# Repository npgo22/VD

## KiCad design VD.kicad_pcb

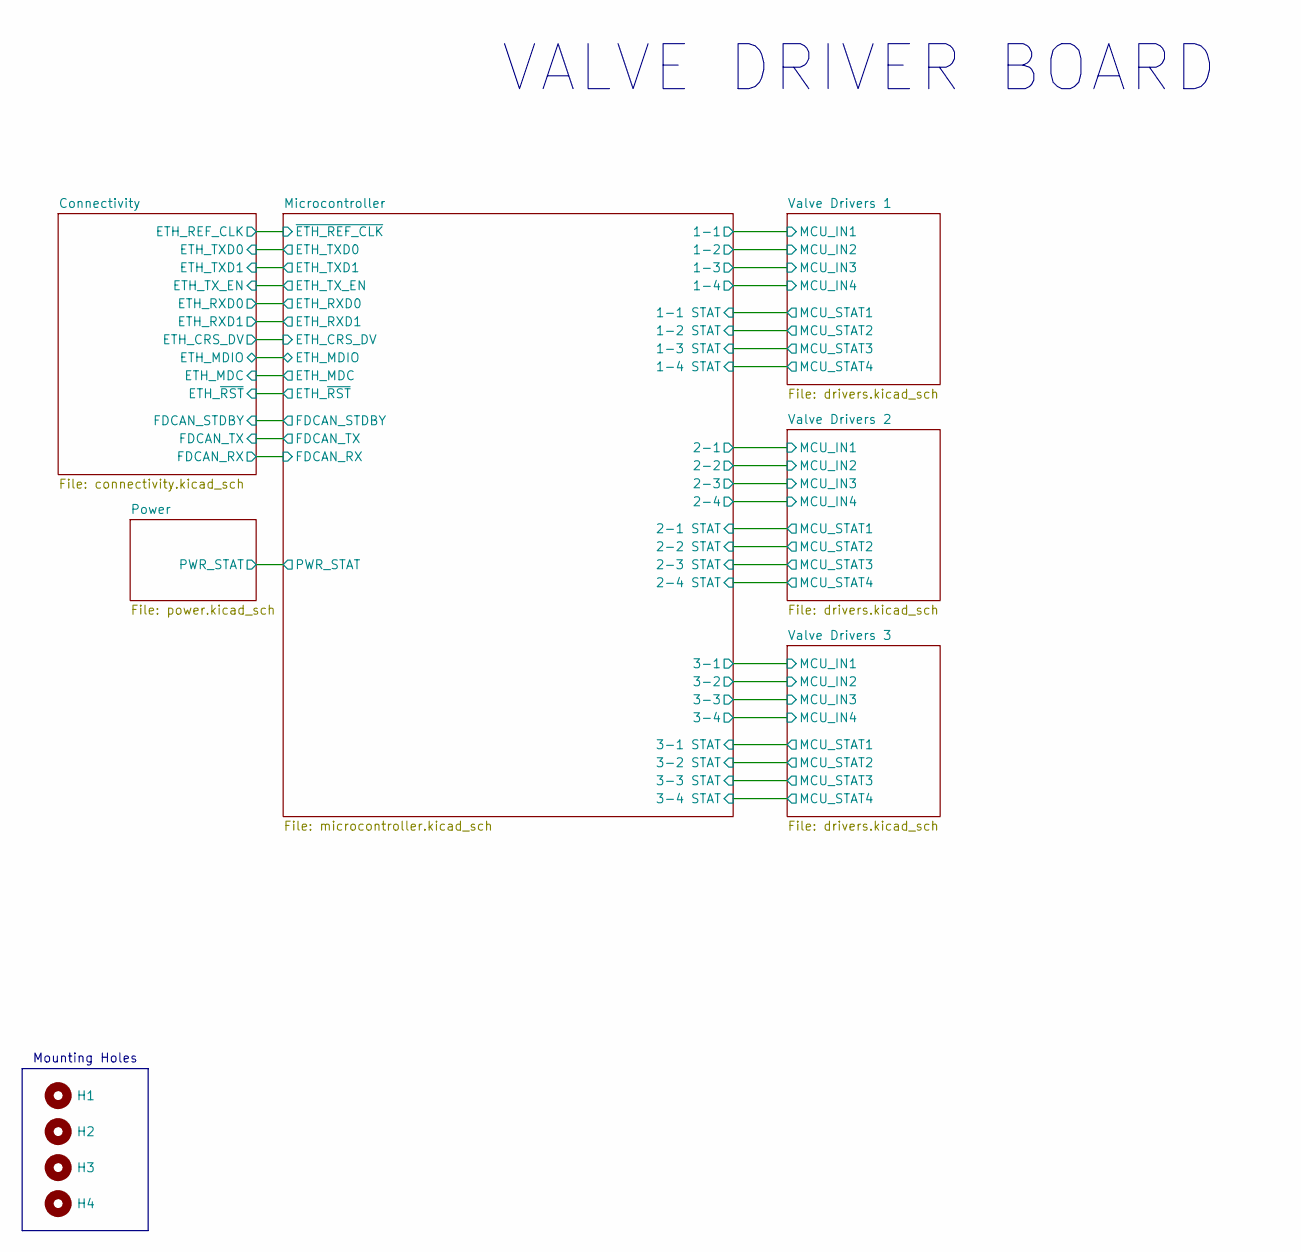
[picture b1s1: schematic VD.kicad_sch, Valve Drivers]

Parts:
H1, H2, H3, H4: MountingHole; MountingHole_3.2mm_M3

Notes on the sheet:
VALVE DRIVER BOARD
Mounting Holes

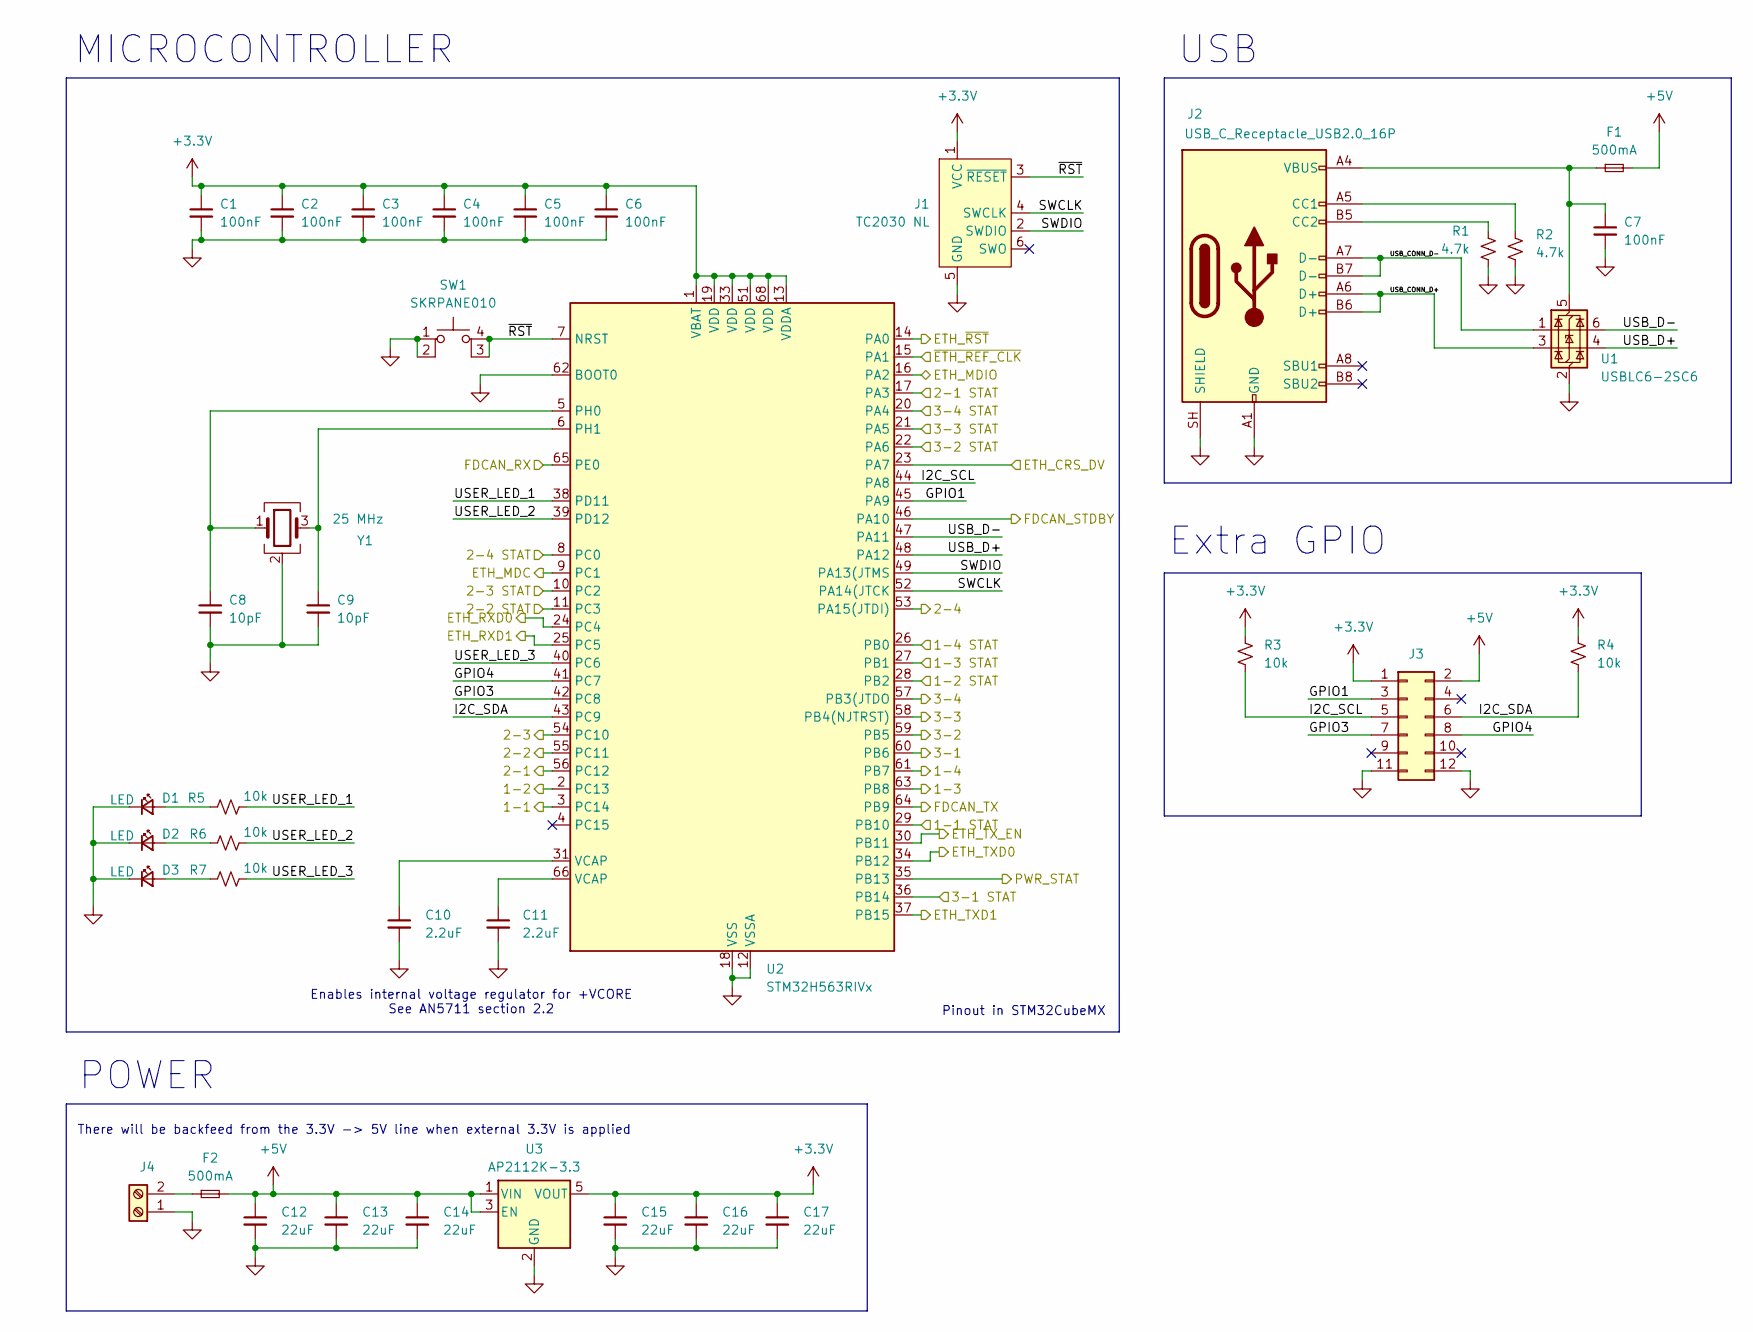
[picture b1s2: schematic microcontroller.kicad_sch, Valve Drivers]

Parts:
C1, C2, C3, C4, C5, C6, C7: 100nF; C_0603
C8, C9: 10pF; C_0603
C10, C11: 2.2uF; C_0603
C12, C13, C14, C15, C16, C17: 22uF; C_0805
D1, D2, D3: LED; LED_0603
F1, F2: 500mA; Fuse_0805_2012Metric
J1: TC2030 NL; Tag-Connect_TC2030-IDC-NL_2x03_P1.27mm_Vertical
J2: USB_C_Receptacle_USB2.0_16P; USB_C_Receptacle_HRO_TYPE-C-31-M-12
J3: Conn_02x06_Top_Bottom; IDC-Header_2x06_P2.54mm_Vertical
J4: Screw_Terminal_01x02; TerminalBlock_Phoenix_MPT-0,5-2-2.54_1x02_P2.54mm_Horizontal
R1, R2: 4.7k; R_0603
R3, R4, R5, R6, R7: 10k; R_0603
SW1: SKRPANE010
U1: USBLC6-2SC6; SOT-23-6
U2: STM32H563RIVx; QFN-68-1EP_8x8mm_P0.4mm_EP6.4x6.4mm
U3: AP2112K-3.3; SOT-23-5
Y1: 25 MHz; 3225-4P-L

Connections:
+3.3V: C1.1, C2.1, C3.1, C4.1, C5.1, C6.1, C15.1, C16.1, C17.1, J1.1 (VCC), J3.1, R3.1, R4.1, U2.1 (VBAT), U2.13 (VDDA), U2.19 (VDD), U2.33 (VDD), U2.51 (VDD), U2.68 (VDD), U3.5 (VOUT); also elsewhere on the board
+5V: C12.1, C13.1, C14.1, F1.2, F2.2, J3.2, U3.1 (VIN), U3.3 (EN); also elsewhere on the board
/Connectivity/ETH_CRS_DV: U2.23 (PA7); also elsewhere on the board
/Connectivity/ETH_MDC: U2.9 (PC1); also elsewhere on the board
/Connectivity/ETH_MDIO: U2.16 (PA2); also elsewhere on the board
/Connectivity/ETH_REF_CLK: U2.15 (PA1); also elsewhere on the board
/Connectivity/ETH_RXD0: U2.24 (PC4); also elsewhere on the board
/Connectivity/ETH_RXD1: U2.25 (PC5); also elsewhere on the board
/Connectivity/ETH_TXD0: U2.34 (PB12); also elsewhere on the board
/Connectivity/ETH_TXD1: U2.37 (PB15); also elsewhere on the board
/Connectivity/ETH_TX_EN: U2.30 (PB11); also elsewhere on the board
/Connectivity/ETH_~RST: U2.14 (PA0); also elsewhere on the board
/Connectivity/FDCAN_RX: U2.65 (PE0); also elsewhere on the board
/Connectivity/FDCAN_STDBY: U2.46 (PA10); also elsewhere on the board
/Connectivity/FDCAN_TX: U2.64 (PB9); also elsewhere on the board
/Microcontroller/1-1: U2.3 (PC14); also elsewhere on the board
/Microcontroller/1-1 STAT: U2.29 (PB10); also elsewhere on the board
/Microcontroller/1-2: U2.2 (PC13); also elsewhere on the board
/Microcontroller/1-2 STAT: U2.28 (PB2); also elsewhere on the board
/Microcontroller/1-3: U2.63 (PB8); also elsewhere on the board
/Microcontroller/1-3 STAT: U2.27 (PB1); also elsewhere on the board
/Microcontroller/1-4: U2.61 (PB7); also elsewhere on the board
/Microcontroller/1-4 STAT: U2.26 (PB0); also elsewhere on the board
/Microcontroller/2-1: U2.56 (PC12); also elsewhere on the board
/Microcontroller/2-1 STAT: U2.17 (PA3); also elsewhere on the board
/Microcontroller/2-2: U2.55 (PC11); also elsewhere on the board
/Microcontroller/2-2 STAT: U2.11 (PC3); also elsewhere on the board
/Microcontroller/2-3: U2.54 (PC10); also elsewhere on the board
/Microcontroller/2-3 STAT: U2.10 (PC2); also elsewhere on the board
/Microcontroller/2-4: U2.53 (PA15(JTDI)); also elsewhere on the board
/Microcontroller/2-4 STAT: U2.8 (PC0); also elsewhere on the board
/Microcontroller/3-1: U2.60 (PB6); also elsewhere on the board
/Microcontroller/3-1 STAT: U2.36 (PB14); also elsewhere on the board
/Microcontroller/3-2: U2.59 (PB5); also elsewhere on the board
/Microcontroller/3-2 STAT: U2.22 (PA6); also elsewhere on the board
/Microcontroller/3-3: U2.58 (PB4(NJTRST)); also elsewhere on the board
/Microcontroller/3-3 STAT: U2.21 (PA5); also elsewhere on the board
/Microcontroller/3-4: U2.57 (PB3(JTDO); also elsewhere on the board
/Microcontroller/3-4 STAT: U2.20 (PA4); also elsewhere on the board
/Microcontroller/GPIO1: J3.3, U2.45 (PA9)
/Microcontroller/GPIO3: J3.7, U2.42 (PC8)
/Microcontroller/GPIO4: J3.8, U2.41 (PC7)
/Microcontroller/I2C_SCL: J3.5, R3.2, U2.44 (PA8)
/Microcontroller/I2C_SDA: J3.6, R4.2, U2.43 (PC9)
/Microcontroller/PWR_STAT: U2.35 (PB13); also elsewhere on the board
/Microcontroller/SWCLK: J1.4 (SWCLK), U2.52 (PA14(JTCK)
/Microcontroller/SWDIO: J1.2 (SWDIO), U2.49 (PA13(JTMS)
/Microcontroller/USB_CONN_D+: J2.A6 (D+), J2.B6 (D+), U1.3 (I/O2)
/Microcontroller/USB_CONN_D-: J2.A7 (D-), J2.B7 (D-), U1.1 (I/O1)
/Microcontroller/USB_D+: U1.4 (I/O2), U2.48 (PA12)
/Microcontroller/USB_D-: U1.6 (I/O1), U2.47 (PA11)
/Microcontroller/USER_LED_1: R5.2, U2.38 (PD11)
/Microcontroller/USER_LED_2: R6.2, U2.39 (PD12)
/Microcontroller/USER_LED_3: R7.2, U2.40 (PC6)
/Microcontroller/~RST: J1.3 (~RESET), SW1.3 (K), SW1.4 (A), U2.7 (NRST)
GND: C1.2, C2.2, C3.2, C4.2, C5.2, C6.2, C7.2, C8.2, C9.2, C10.2, C11.2, C12.2, C13.2, C14.2, C15.2, C16.2, C17.2, D1.1 (K), D2.1 (K), D3.1 (K), J1.5 (GND), J2.A1 (GND), J2.A12 (GND), J2.B1 (GND), J2.B12 (GND), J2.SH (SHIELD), J3.11, J3.12, J4.1, R1.1, R2.2, SW1.1, SW1.2, U1.2 (GND), U2.12 (VSSA), U2.18 (VSS), U2.32 (VSS), U2.50 (VSS), U2.62 (BOOT0), U2.67 (VSS), U2.69 (VSS), U3.2 (GND), Y1.2 (G), Y1.4 (G); also elsewhere on the board
unnamed: C10.1, U2.31 (VCAP)
unnamed: C11.1, U2.66 (VCAP)
unnamed: D1.2 (A), R5.1
unnamed: D2.2 (A), R6.1
unnamed: D3.2 (A), R7.1
unnamed: J2.A5 (CC1), R2.1
unnamed: J2.B5 (CC2), R1.2
unnamed: F2.1, J4.2
unnamed: C7.1, F1.1, J2.A4 (VBUS), J2.A9 (VBUS), J2.B4 (VBUS), J2.B9 (VBUS), U1.5 (VBUS)
unnamed: C8.1, U2.5 (PH0), Y1.1
unnamed: C9.1, U2.6 (PH1), Y1.3

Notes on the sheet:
Enables internal voltage regulator for +VCORE See AN5711 section 2.2
MICROCONTROLLER
There will be backfeed from the 3.3V -> 5V line when external 3.3V is applied
Extra GPIO
USB
POWER
Pinout in STM32CubeMX

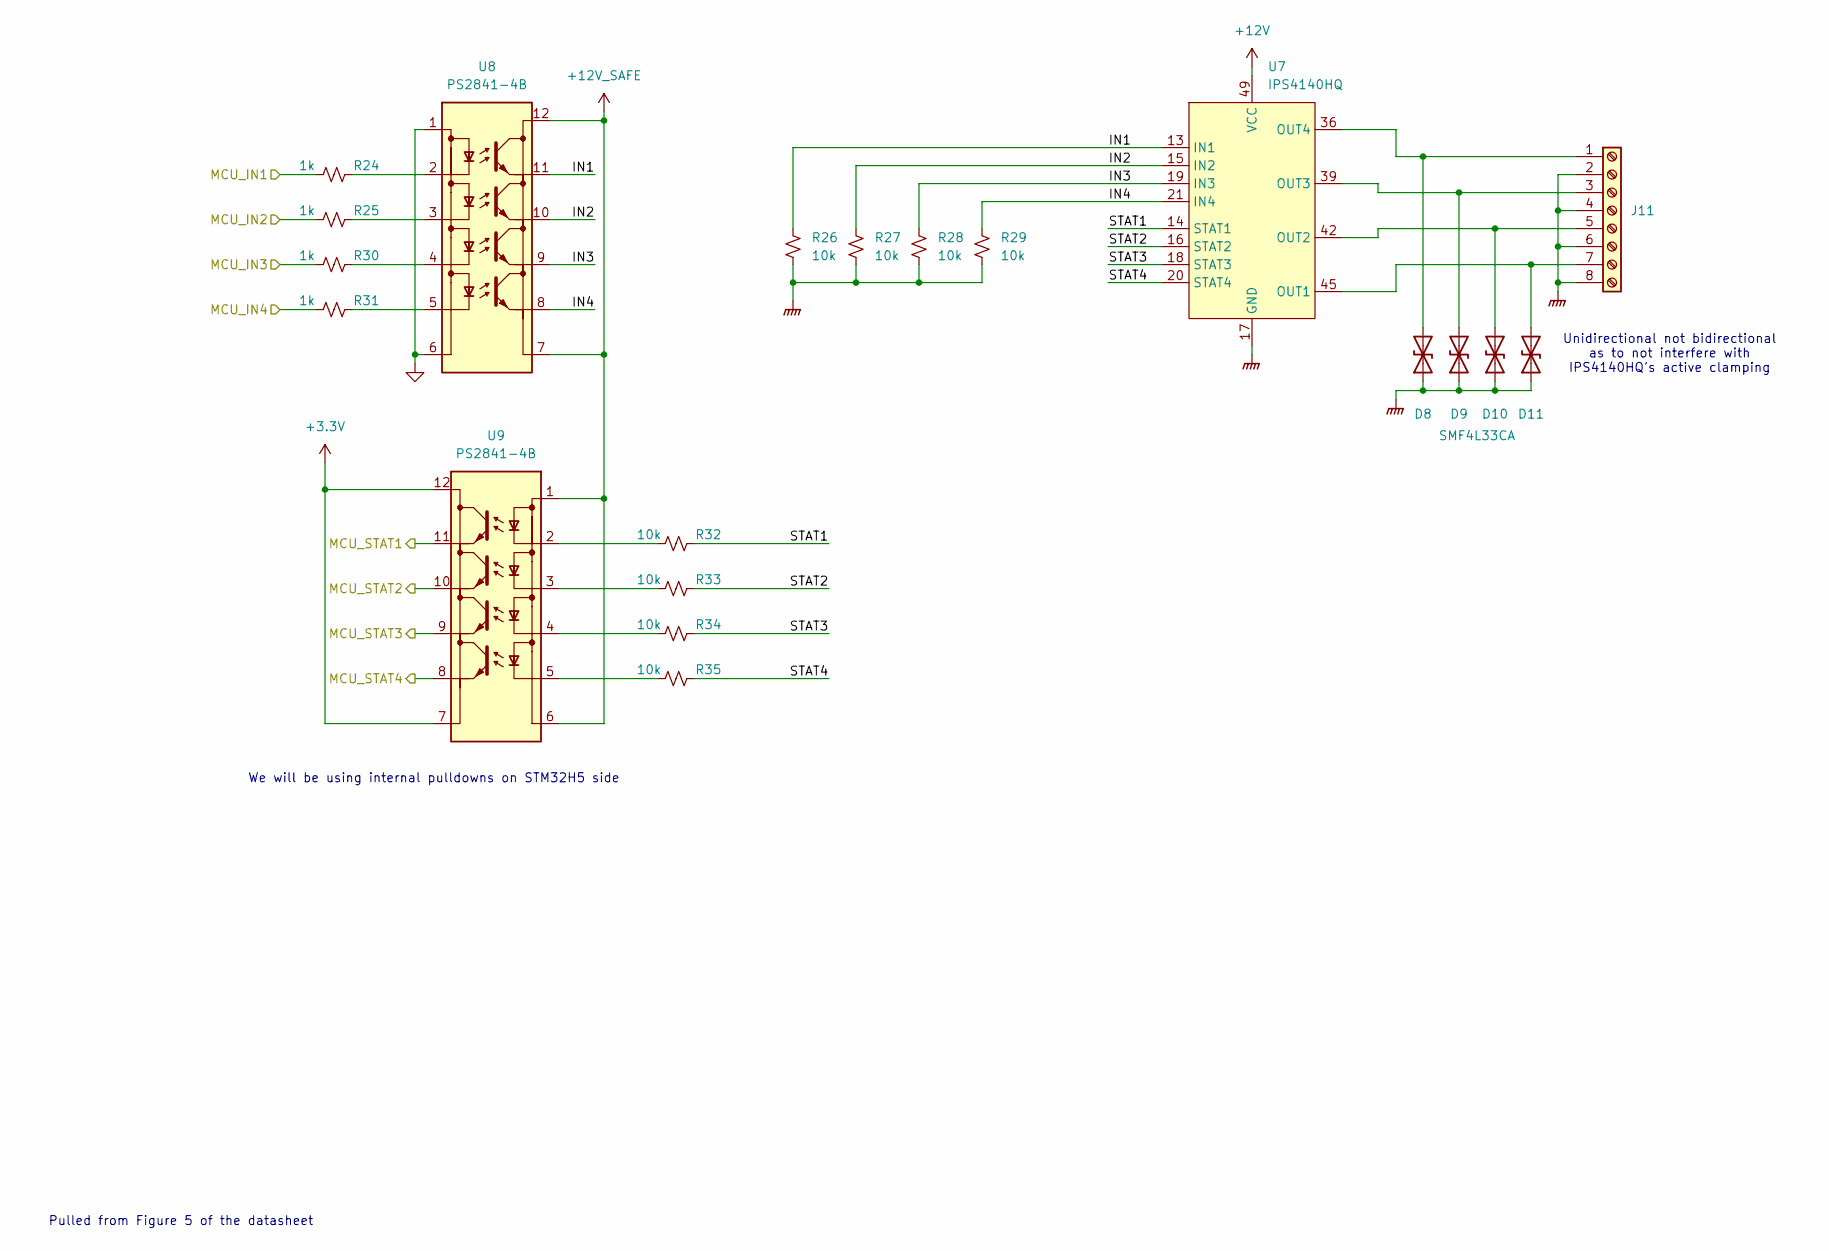
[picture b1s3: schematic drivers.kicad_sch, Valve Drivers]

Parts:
D8, D9, D10, D11: SMF4L33CA; D_SOD-123F
J11: Screw_Terminal_01x08; TerminalBlock_Phoenix_MPT-0,5-8-2.54_1x08_P2.54mm_Horizontal
R24, R25, R30, R31: 1k; R_0603
R26, R27, R28, R29, R32, R33, R34, R35: 10k; R_0603
U7: IPS4140HQ; QFN-48_EP_9.01x7.01_Pitch0.5mm
U8, U9: PS2841-4B; SOIC-12

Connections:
+3.3V: U9.7, U9.12; also elsewhere on the board
+12V: U7.49 (VCC); also elsewhere on the board
+12V_SAFE: U8.7, U8.12, U9.1, U9.6; also elsewhere on the board
/Microcontroller/1-1: R24.1; also elsewhere on the board
/Microcontroller/1-1 STAT: U9.11; also elsewhere on the board
/Microcontroller/1-2: R25.1; also elsewhere on the board
/Microcontroller/1-2 STAT: U9.10; also elsewhere on the board
/Microcontroller/1-3: R30.1; also elsewhere on the board
/Microcontroller/1-3 STAT: U9.9; also elsewhere on the board
/Microcontroller/1-4: R31.1; also elsewhere on the board
/Microcontroller/1-4 STAT: U9.8; also elsewhere on the board
/Valve Drivers 1/IN1: R26.1, U7.13 (IN1), U8.11
/Valve Drivers 1/IN2: R27.1, U7.15 (IN2), U8.10
/Valve Drivers 1/IN3: R28.1, U7.19 (IN3), U8.9
/Valve Drivers 1/IN4: R29.1, U7.21 (IN4), U8.8
/Valve Drivers 1/STAT1: R32.2, U7.14 (STAT1)
/Valve Drivers 1/STAT2: R33.2, U7.16 (STAT2)
/Valve Drivers 1/STAT3: R34.2, U7.18 (STAT3)
/Valve Drivers 1/STAT4: R35.2, U7.20 (STAT4)
GND: U8.1, U8.6; also elsewhere on the board
GNDPWR: D8.1 (A1), D9.1 (A1), D10.1 (A1), D11.1 (A1), J11.2, J11.4, J11.6, J11.8, R26.2, R27.2, R28.2, R29.2, U7.17 (GND); also elsewhere on the board
unnamed: D8.2 (A2), J11.1, U7.36 (OUT4), U7.37 (OUT4), U7.38 (OUT4)
unnamed: D9.2 (A2), J11.3, U7.39 (OUT3), U7.40 (OUT3), U7.41 (OUT3)
unnamed: D10.2 (A2), J11.5, U7.42 (OUT2), U7.43 (OUT2), U7.44 (OUT2)
unnamed: D11.2 (A2), J11.7, U7.45 (OUT1), U7.46 (OUT1), U7.47 (OUT1)
unnamed: R24.2, U8.2
unnamed: R25.2, U8.3
unnamed: R30.2, U8.4
unnamed: R31.2, U8.5
unnamed: R32.1, U9.2
unnamed: R33.1, U9.3
unnamed: R34.1, U9.4
unnamed: R35.1, U9.5

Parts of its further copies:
D12, D13, D14, D15, D16, D17, D18, D19: SMF4L33CA; D_SOD-123F
J12, J13: Screw_Terminal_01x08; TerminalBlock_Phoenix_MPT-0,5-8-2.54_1x08_P2.54mm_Horizontal
R36, R37, R42, R43, R48, R49, R54, R55: 1k; R_0603
R38, R39, R40, R41, R44, R45, R46, R47, R50, R51, R52, R53, R56, R57, R58, R59: 10k; R_0603
U10, U13: IPS4140HQ; QFN-48_EP_9.01x7.01_Pitch0.5mm
U11, U12, U14, U15: PS2841-4B; SOIC-12

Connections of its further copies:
+3.3V: U12.7, U12.12, U15.7, U15.12; also elsewhere on the board
+12V: U10.49 (VCC), U13.49 (VCC); also elsewhere on the board
+12V_SAFE: U11.7, U11.12, U12.1, U12.6, U14.7, U14.12, U15.1, U15.6; also elsewhere on the board
/Microcontroller/2-1: R36.1; also elsewhere on the board
/Microcontroller/2-1 STAT: U12.11; also elsewhere on the board
/Microcontroller/2-2: R37.1; also elsewhere on the board
/Microcontroller/2-2 STAT: U12.10; also elsewhere on the board
/Microcontroller/2-3: R42.1; also elsewhere on the board
/Microcontroller/2-3 STAT: U12.9; also elsewhere on the board
/Microcontroller/2-4: R43.1; also elsewhere on the board
/Microcontroller/2-4 STAT: U12.8; also elsewhere on the board
/Microcontroller/3-1: R48.1; also elsewhere on the board
/Microcontroller/3-1 STAT: U15.11; also elsewhere on the board
/Microcontroller/3-2: R49.1; also elsewhere on the board
/Microcontroller/3-2 STAT: U15.10; also elsewhere on the board
/Microcontroller/3-3: R54.1; also elsewhere on the board
/Microcontroller/3-3 STAT: U15.9; also elsewhere on the board
/Microcontroller/3-4: R55.1; also elsewhere on the board
/Microcontroller/3-4 STAT: U15.8; also elsewhere on the board
/Valve Drivers 2/IN1: R38.1, U10.13 (IN1), U11.11
/Valve Drivers 2/IN2: R39.1, U10.15 (IN2), U11.10
/Valve Drivers 2/IN3: R40.1, U10.19 (IN3), U11.9
/Valve Drivers 2/IN4: R41.1, U10.21 (IN4), U11.8
/Valve Drivers 2/STAT1: R44.2, U10.14 (STAT1)
/Valve Drivers 2/STAT2: R45.2, U10.16 (STAT2)
/Valve Drivers 2/STAT3: R46.2, U10.18 (STAT3)
/Valve Drivers 2/STAT4: R47.2, U10.20 (STAT4)
/Valve Drivers 3/IN1: R50.1, U13.13 (IN1), U14.11
/Valve Drivers 3/IN2: R51.1, U13.15 (IN2), U14.10
/Valve Drivers 3/IN3: R52.1, U13.19 (IN3), U14.9
/Valve Drivers 3/IN4: R53.1, U13.21 (IN4), U14.8
/Valve Drivers 3/STAT1: R56.2, U13.14 (STAT1)
/Valve Drivers 3/STAT2: R57.2, U13.16 (STAT2)
/Valve Drivers 3/STAT3: R58.2, U13.18 (STAT3)
/Valve Drivers 3/STAT4: R59.2, U13.20 (STAT4)
GND: U11.1, U11.6, U14.1, U14.6; also elsewhere on the board
GNDPWR: D12.1 (A1), D13.1 (A1), D14.1 (A1), D15.1 (A1), D16.1 (A1), D17.1 (A1), D18.1 (A1), D19.1 (A1), J12.2, J12.4, J12.6, J12.8, J13.2, J13.4, J13.6, J13.8, R38.2, R39.2, R40.2, R41.2, R50.2, R51.2, R52.2, R53.2, U10.17 (GND), U13.17 (GND); also elsewhere on the board
unnamed: D12.2 (A2), J12.1, U10.36 (OUT4), U10.37 (OUT4), U10.38 (OUT4)
unnamed: D13.2 (A2), J12.3, U10.39 (OUT3), U10.40 (OUT3), U10.41 (OUT3)
unnamed: D14.2 (A2), J12.5, U10.42 (OUT2), U10.43 (OUT2), U10.44 (OUT2)
unnamed: D15.2 (A2), J12.7, U10.45 (OUT1), U10.46 (OUT1), U10.47 (OUT1)
unnamed: D16.2 (A2), J13.1, U13.36 (OUT4), U13.37 (OUT4), U13.38 (OUT4)
unnamed: D17.2 (A2), J13.3, U13.39 (OUT3), U13.40 (OUT3), U13.41 (OUT3)
unnamed: D18.2 (A2), J13.5, U13.42 (OUT2), U13.43 (OUT2), U13.44 (OUT2)
unnamed: D19.2 (A2), J13.7, U13.45 (OUT1), U13.46 (OUT1), U13.47 (OUT1)
unnamed: R36.2, U11.2
unnamed: R37.2, U11.3
unnamed: R42.2, U11.4
unnamed: R43.2, U11.5
unnamed: R44.1, U12.2
unnamed: R45.1, U12.3
unnamed: R46.1, U12.4
unnamed: R47.1, U12.5
unnamed: R48.2, U14.2
unnamed: R49.2, U14.3
unnamed: R54.2, U14.4
unnamed: R55.2, U14.5
unnamed: R56.1, U15.2
unnamed: R57.1, U15.3
unnamed: R58.1, U15.4
unnamed: R59.1, U15.5

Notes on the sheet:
Unidirectional not bidirectional as to not interfere with IPS4140HQ's active clamping
We will be using internal pulldowns on STM32H5 side
Pulled from Figure 5 of the datasheet

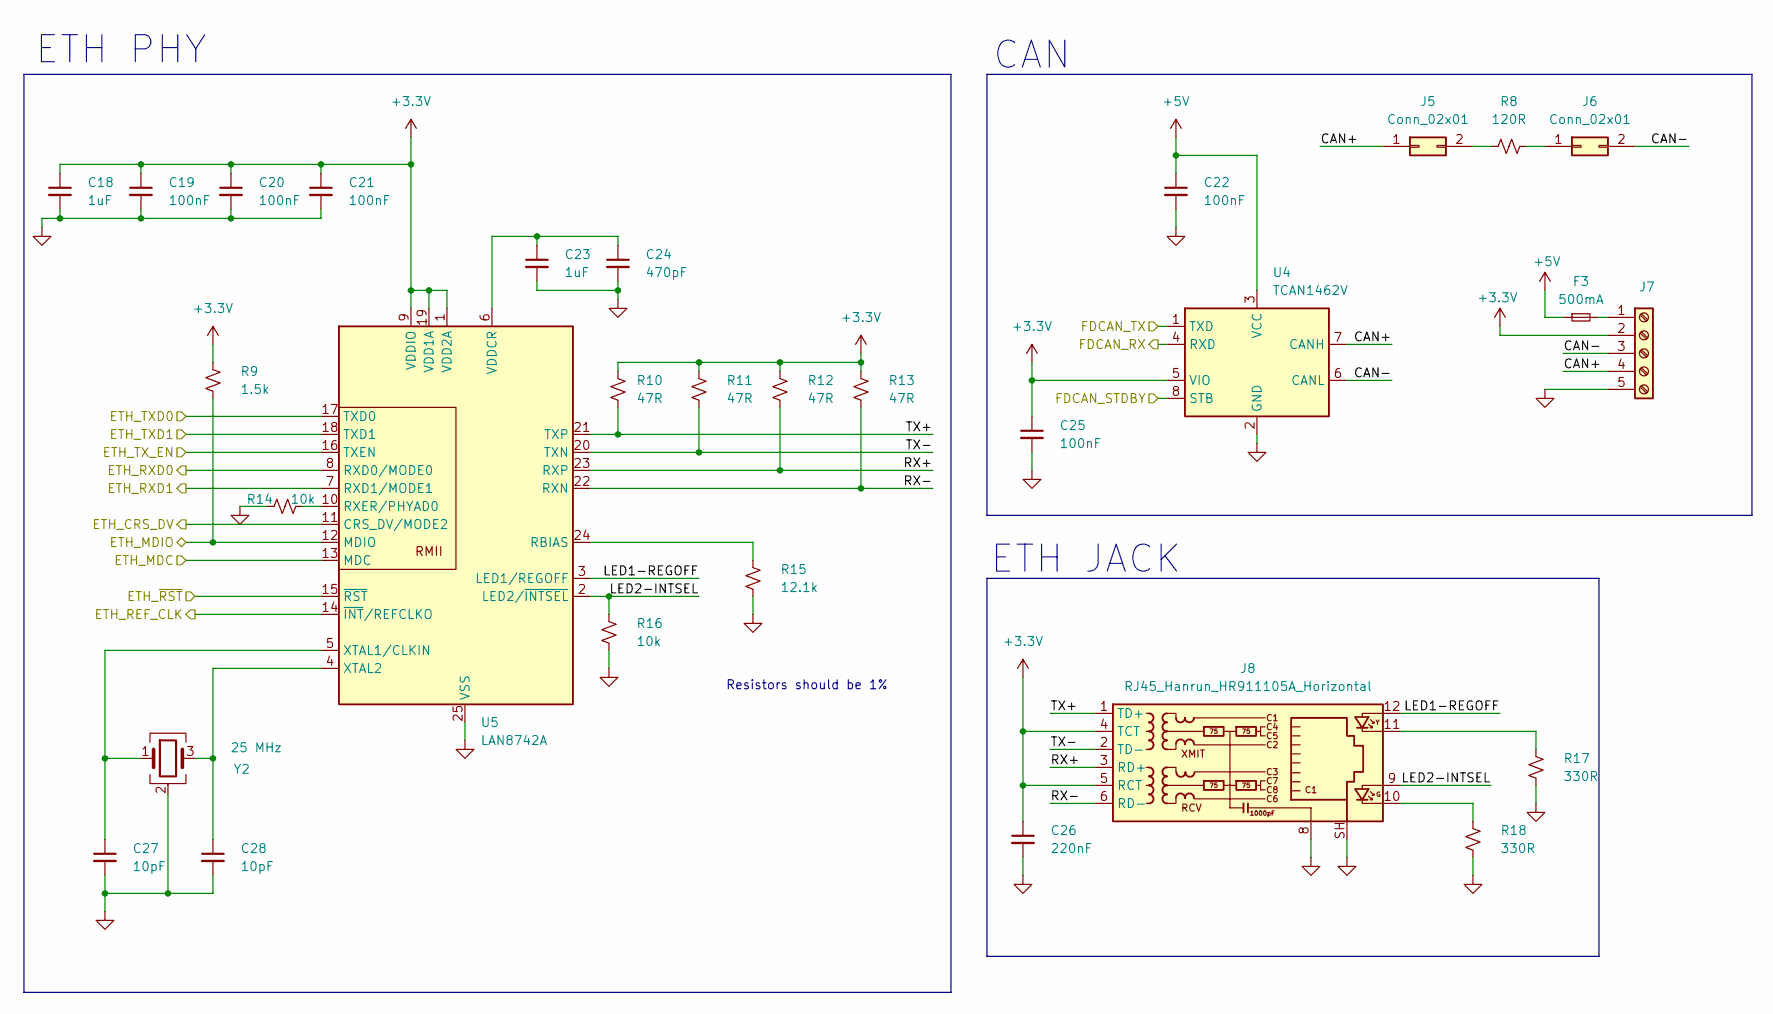
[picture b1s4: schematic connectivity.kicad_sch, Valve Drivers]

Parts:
C18, C23: 1uF; C_0603
C19, C20, C21, C22, C25: 100nF; C_0603
C24: 470pF; C_0603
C26: 220nF; C_0603
C27, C28: 10pF; C_0603
F3: 500mA; Fuse_0805_2012Metric
J5, J6: Conn_02x01; PinHeader_2x01_P2.54mm_Vertical
J7: Screw_Terminal_01x05; TerminalBlock_Phoenix_MPT-0,5-5-2.54_1x05_P2.54mm_Horizontal
J8: RJ45_Hanrun_HR911105A_Horizontal
R8: 120R; R_0603
R9: 1.5k; R_0603
R10, R11, R12, R13: 47R; R_0603
R14, R16: 10k; R_0603
R15: 12.1k; R_0603
R17, R18: 330R; R_0603
U4: TCAN1462V; SOIC-8_3.9x4.9mm_P1.27mm
U5: LAN8742A; VQFN-24-1EP_4x4mm_P0.5mm_EP2.5x2.5mm_ThermalVias
Y2: 25 MHz; 3225-4P-L

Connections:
+3.3V: C18.1, C19.1, C20.1, C21.1, C25.1, C26.1, J7.2, J8.4 (TCT), J8.5 (RCT), R9.1, R10.1, R11.1, R12.1, R13.1, U4.5 (VIO), U5.1 (VDD2A), U5.9 (VDDIO), U5.19 (VDD1A); also elsewhere on the board
+5V: C22.1, F3.1, U4.3 (VCC); also elsewhere on the board
/Connectivity/CAN+: J5.1, J7.4, U4.7 (CANH)
/Connectivity/CAN-: J6.2, J7.3, U4.6 (CANL)
/Connectivity/ETH_CRS_DV: U5.11 (CRS_DV/MODE2); also elsewhere on the board
/Connectivity/ETH_MDC: U5.13 (MDC); also elsewhere on the board
/Connectivity/ETH_MDIO: R9.2, U5.12 (MDIO); also elsewhere on the board
/Connectivity/ETH_REF_CLK: U5.14 (~INT/REFCLKO); also elsewhere on the board
/Connectivity/ETH_RXD0: U5.8 (RXD0/MODE0); also elsewhere on the board
/Connectivity/ETH_RXD1: U5.7 (RXD1/MODE1); also elsewhere on the board
/Connectivity/ETH_TXD0: U5.17 (TXD0); also elsewhere on the board
/Connectivity/ETH_TXD1: U5.18 (TXD1); also elsewhere on the board
/Connectivity/ETH_TX_EN: U5.16 (TXEN); also elsewhere on the board
/Connectivity/ETH_~RST: U5.15 (~RST); also elsewhere on the board
/Connectivity/FDCAN_RX: U4.4 (RXD); also elsewhere on the board
/Connectivity/FDCAN_STDBY: U4.8 (STB); also elsewhere on the board
/Connectivity/FDCAN_TX: U4.1 (TXD); also elsewhere on the board
/Connectivity/LED1-REGOFF: J8.12, U5.3 (LED1/REGOFF)
/Connectivity/LED2-INTSEL: J8.9, R16.1, U5.2 (LED2/~INTSEL)
/Connectivity/RX+: J8.3 (RD+), R12.2, U5.23 (RXP)
/Connectivity/RX-: J8.6 (RD-), R13.2, U5.22 (RXN)
/Connectivity/TX+: J8.1 (TD+), R10.2, U5.21 (TXP)
/Connectivity/TX-: J8.2 (TD-), R11.2, U5.20 (TXN)
GND: C18.2, C19.2, C20.2, C21.2, C22.2, C23.2, C24.2, C25.2, C26.2, C27.2, C28.2, J7.5, J8.8, J8.SH, R14.1, R15.2, R16.2, R17.2, R18.2, U4.2 (GND), U5.25 (VSS), Y2.2 (G), Y2.4 (G); also elsewhere on the board
unnamed: J5.2, R8.1
unnamed: J6.1, R8.2
unnamed: F3.2, J7.1
unnamed: J8.10, R18.1
unnamed: J8.11, R17.1
unnamed: R15.1, U5.24 (RBIAS)
unnamed: R14.2, U5.10 (RXER/PHYAD0)
unnamed: C23.1, C24.1, U5.6 (VDDCR)
unnamed: C27.1, U5.5 (XTAL1/CLKIN), Y2.1
unnamed: C28.1, U5.4 (XTAL2), Y2.3

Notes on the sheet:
ETH PHY
CAN
Resistors should be 1%
ETH JACK

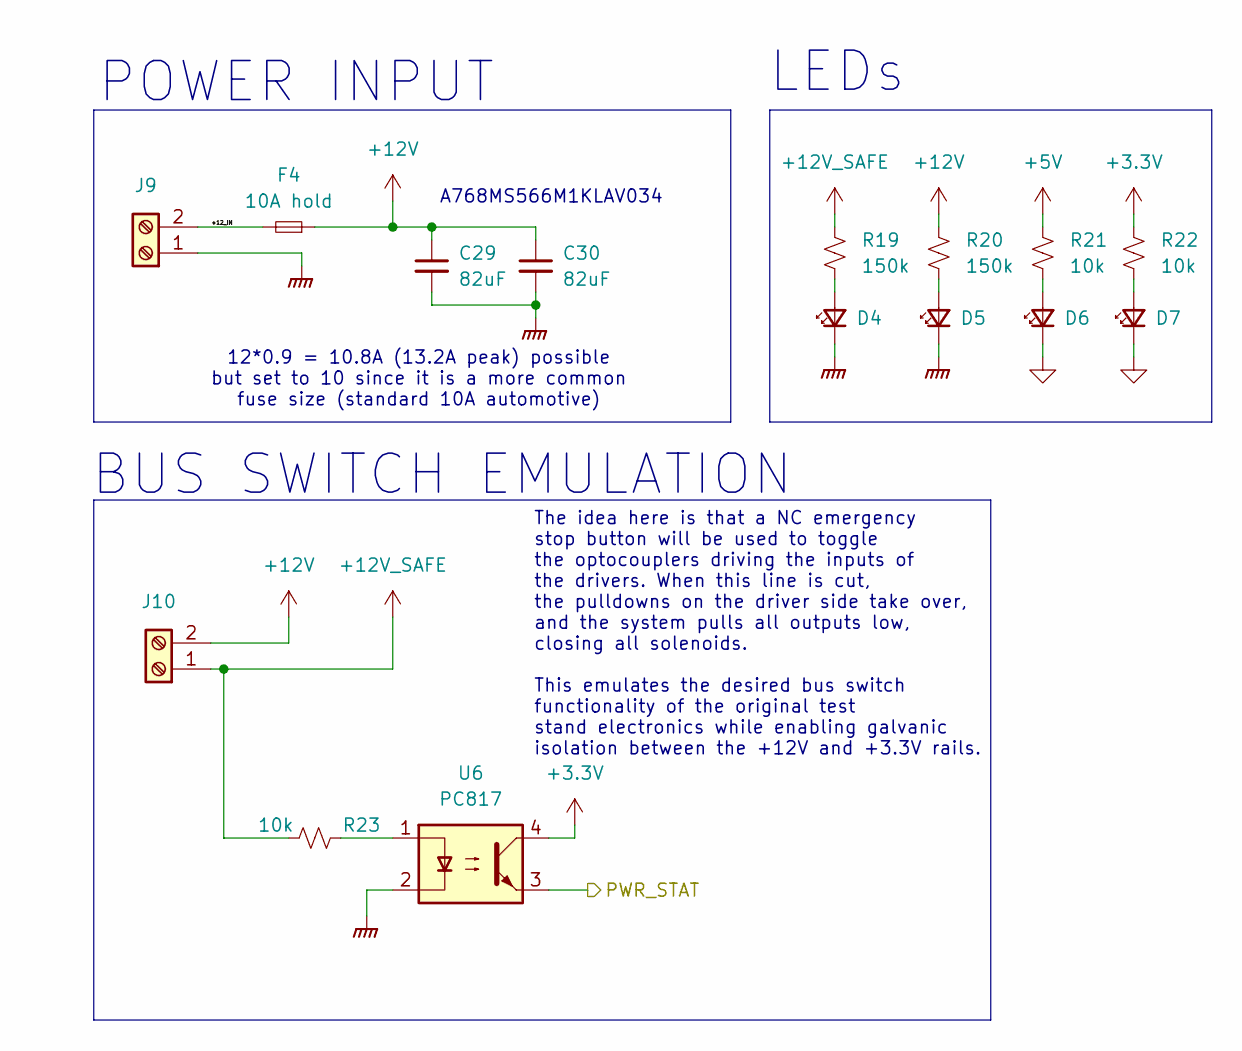
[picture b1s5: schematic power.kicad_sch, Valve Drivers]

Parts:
C29, C30: 82uF; Yageo Polymer MS
D4, D5, D6, D7: LED; LED_0603
F4: 10A hold; FuseHolder_Blade_ATO_Littelfuse_FLR_178.6165
J9: Screw_Terminal_01x02; TerminalBlock_Phoenix_MKDS-1,5-2-5.08_1x02_P5.08mm_Horizont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
J10: Screw_Terminal_01x02; TerminalBlock_Phoenix_MPT-0,5-2-2.54_1x02_P2.54mm_Horizontal
R19, R20: 150k; R_0603
R21, R22, R23: 10k; R_0603
U6: PC817; DIP-4_W7.62mm_SMDSocket_SmallPads

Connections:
+3.3V: R22.1, U6.4; also elsewhere on the board
+5V: R21.1; also elsewhere on the board
+12V: C29.1, C30.1, F4.1, J10.2, R20.1; also elsewhere on the board
+12V_SAFE: J10.1, R19.1, R23.1; also elsewhere on the board
/Microcontroller/PWR_STAT: U6.3; also elsewhere on the board
/Power/+12_IN: F4.2, J9.2
GND: D6.1 (K), D7.1 (K); also elsewhere on the board
GNDPWR: C29.2, C30.2, D4.1 (K), D5.1 (K), J9.1, U6.2; also elsewhere on the board
unnamed: D4.2 (A), R19.2
unnamed: D5.2 (A), R20.2
unnamed: D6.2 (A), R21.2
unnamed: D7.2 (A), R22.2
unnamed: R23.2, U6.1

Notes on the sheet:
LEDs
A768MS566M1KLAV034
The idea here is that a NC emergency stop button will be used to toggle the optocouplers driving the inputs of the drivers. When this line is cut, the pulldowns on the driver side take over, and the system pulls all outputs low, closing all solenoids. This emulates the desired bus switch functional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
POWER INPUT
12*0.9 = 10.8A (13.2A peak) possible but set to 10 since it is a more common fuse size (standard 10A automotive)
BUS SWITCH EMULATION

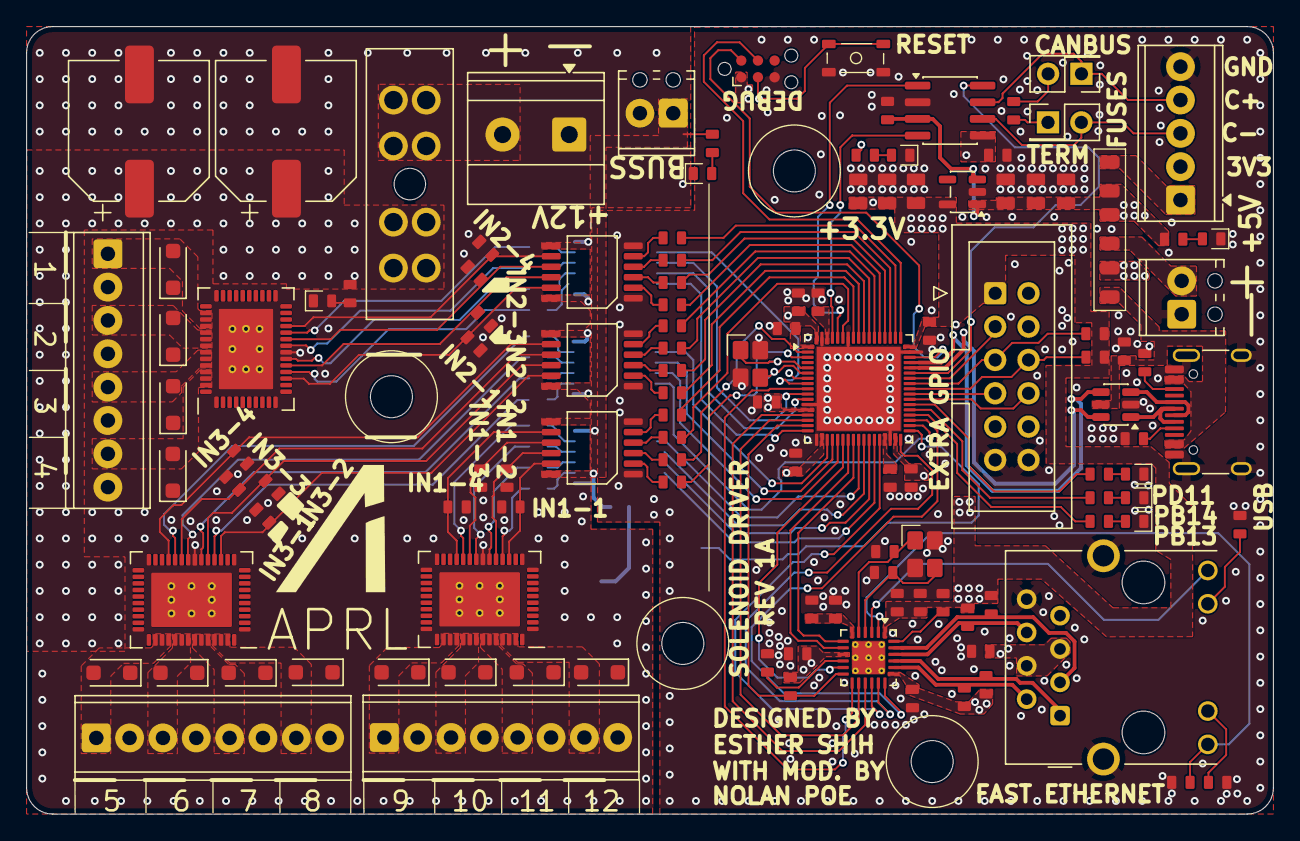
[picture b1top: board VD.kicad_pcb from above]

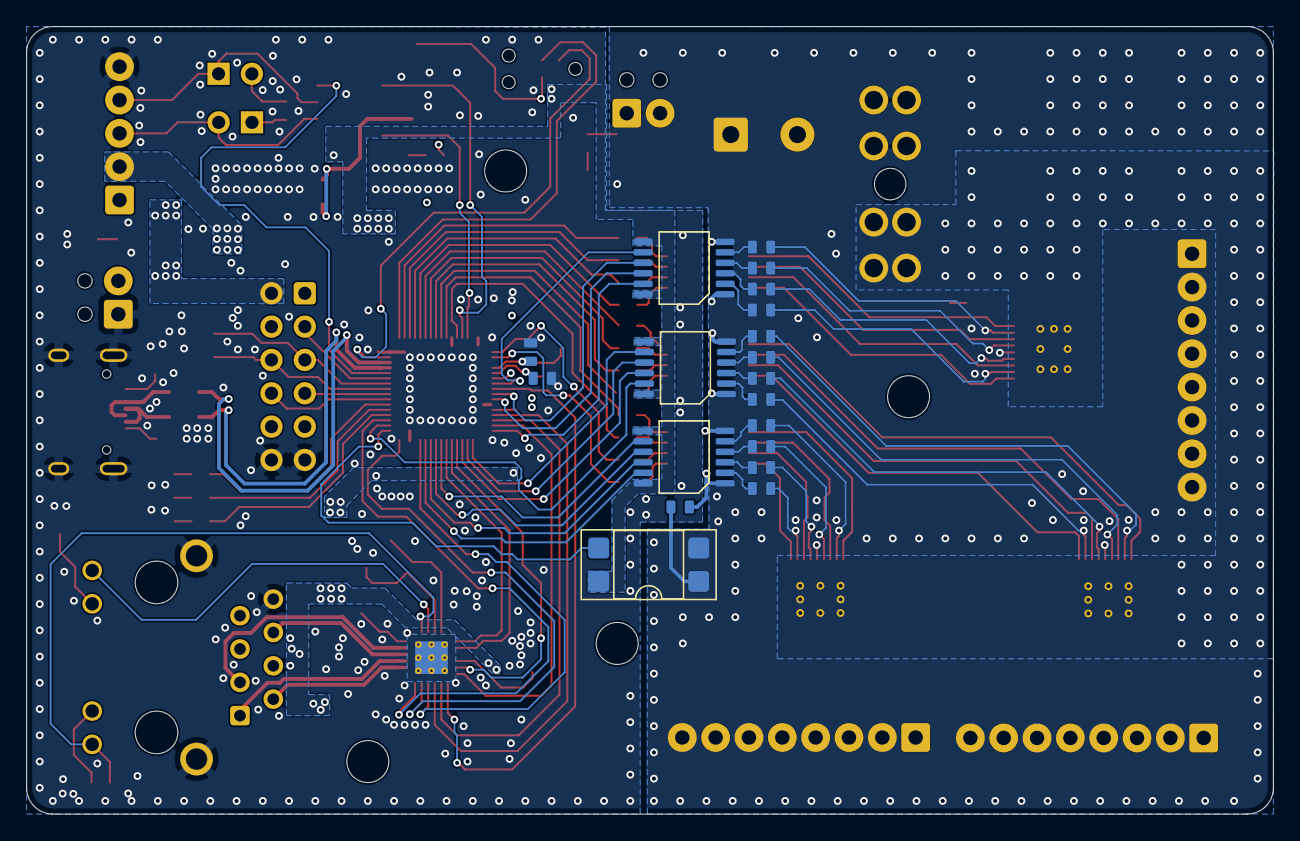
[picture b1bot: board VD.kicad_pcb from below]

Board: 4 copper layers, 95.0 x 60.0 mm, 147 parts (19 on the bottom side), 154 nets.

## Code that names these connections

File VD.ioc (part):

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Mcu.Name=STM32H563RIVx
Mcu.Package=VFQFPN68
Mcu.UserName=STM32H563RIVx
PA1.Mode=RMII
PA1.Signal=ETH_REF_CLK
PA11.Mode=Device
PA11.Signal=USB_DM
PA12.Mode=Device
PA12.Signal=USB_DP
PA13(JTMS/SWDIO).Mode=Serial_Wire
PA13(JTMS/SWDIO).Signal=DEBUG_JTMS-SWDIO
PA14(JTCK/SWCLK).Mode=Serial_Wire
PA14(JTCK/SWCLK).Signal=DEBUG_JTCK-SWCLK
PA2.Mode=RMII
PA2.Signal=ETH_MDIO
PA3.GPIOParameters=GPIO_Label
PA3.GPIO_Label=ETH_nRST
PA3.Signal=GPIO_Output
PA4.GPIOParameters=GPIO_Label
PA4.GPIO_Label=ADC2 nDRDY
PA4.Signal=GPIO_Input
PA5.GPIOParameters=GPIO_Label
PA5.GPIO_Label=ADC2 nDONE
PA5.Signal=GPIO_Input
PA6.GPIOParameters=GPIO_Label
PA6.GPIO_Label=ADC2 nRESET
PA6.Signal=GPIO_Output
PA7.Mode=RMII
PA7.Signal=ETH_CRS_DV
PA8.Mode=I2C
PA8.Signal=I2C3_SCL
PB11.Mode=RMII
PB11.Signal=ETH_TX_EN
PB12.Mode=RMII
PB12.Signal=ETH_TXD0
PB13.GPIOParameters=GPIO_Label
PB13.GPIO_Label=USER_LED_1
PB13.Signal=GPIO_Output
PB14.GPIOParameters=GPIO_Label
PB14.GPIO_Label=USER_LED_2
PB14.Signal=GPIO_Output
PB15.Mode=RMII
PB15.Signal=ETH_TXD1
PB9.Mode=FDCAN_Activate
PB9.Signal=FDCAN1_TX
PC1.Mode=RMII
PC1.Signal=ETH_MDC
PC4.Mode=RMII
PC4.Signal=ETH_RXD0
PC5.Mode=RMII
PC5.Signal=ETH_RXD1
PC9.Mode=I2C
PC9.Signal=I2C3_SDA
PD11.GPIOParameters=GPIO_Label
PD11.GPIO_Label=USER_LED_3
PD11.Signal=GPIO_Output
PD12.GPIOParameters=GPIO_Label
PD12.GPIO_Label=GPIO6
PD12.Signal=GPIO_Output
PE0.Mode=FDCAN_Activate
PE0.Signal=FDCAN1_RX
PH0-OSC_IN(PH0).Mode=HSE-External-Oscillator
PH0-OSC_IN(PH0).Signal=RCC_OSC_IN
PH1-OSC_OUT(PH1).Mode=HSE-External-Oscillator
PH1-OSC_OUT(PH1).Signal=RCC_OSC_OUT
RCC.HSE_VALUE=25000000
RCC.SYSCLKFreq_VALUE=32000000
board=custom

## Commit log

2026-05-26 Initial commit, still need to update .ioc file and clean up silkscreens
2026-05-26 Update silkscreens and nets
2026-05-26 Small stuff
2026-05-27 Rename kibot yaml
2026-06-29 Add renovate.json
